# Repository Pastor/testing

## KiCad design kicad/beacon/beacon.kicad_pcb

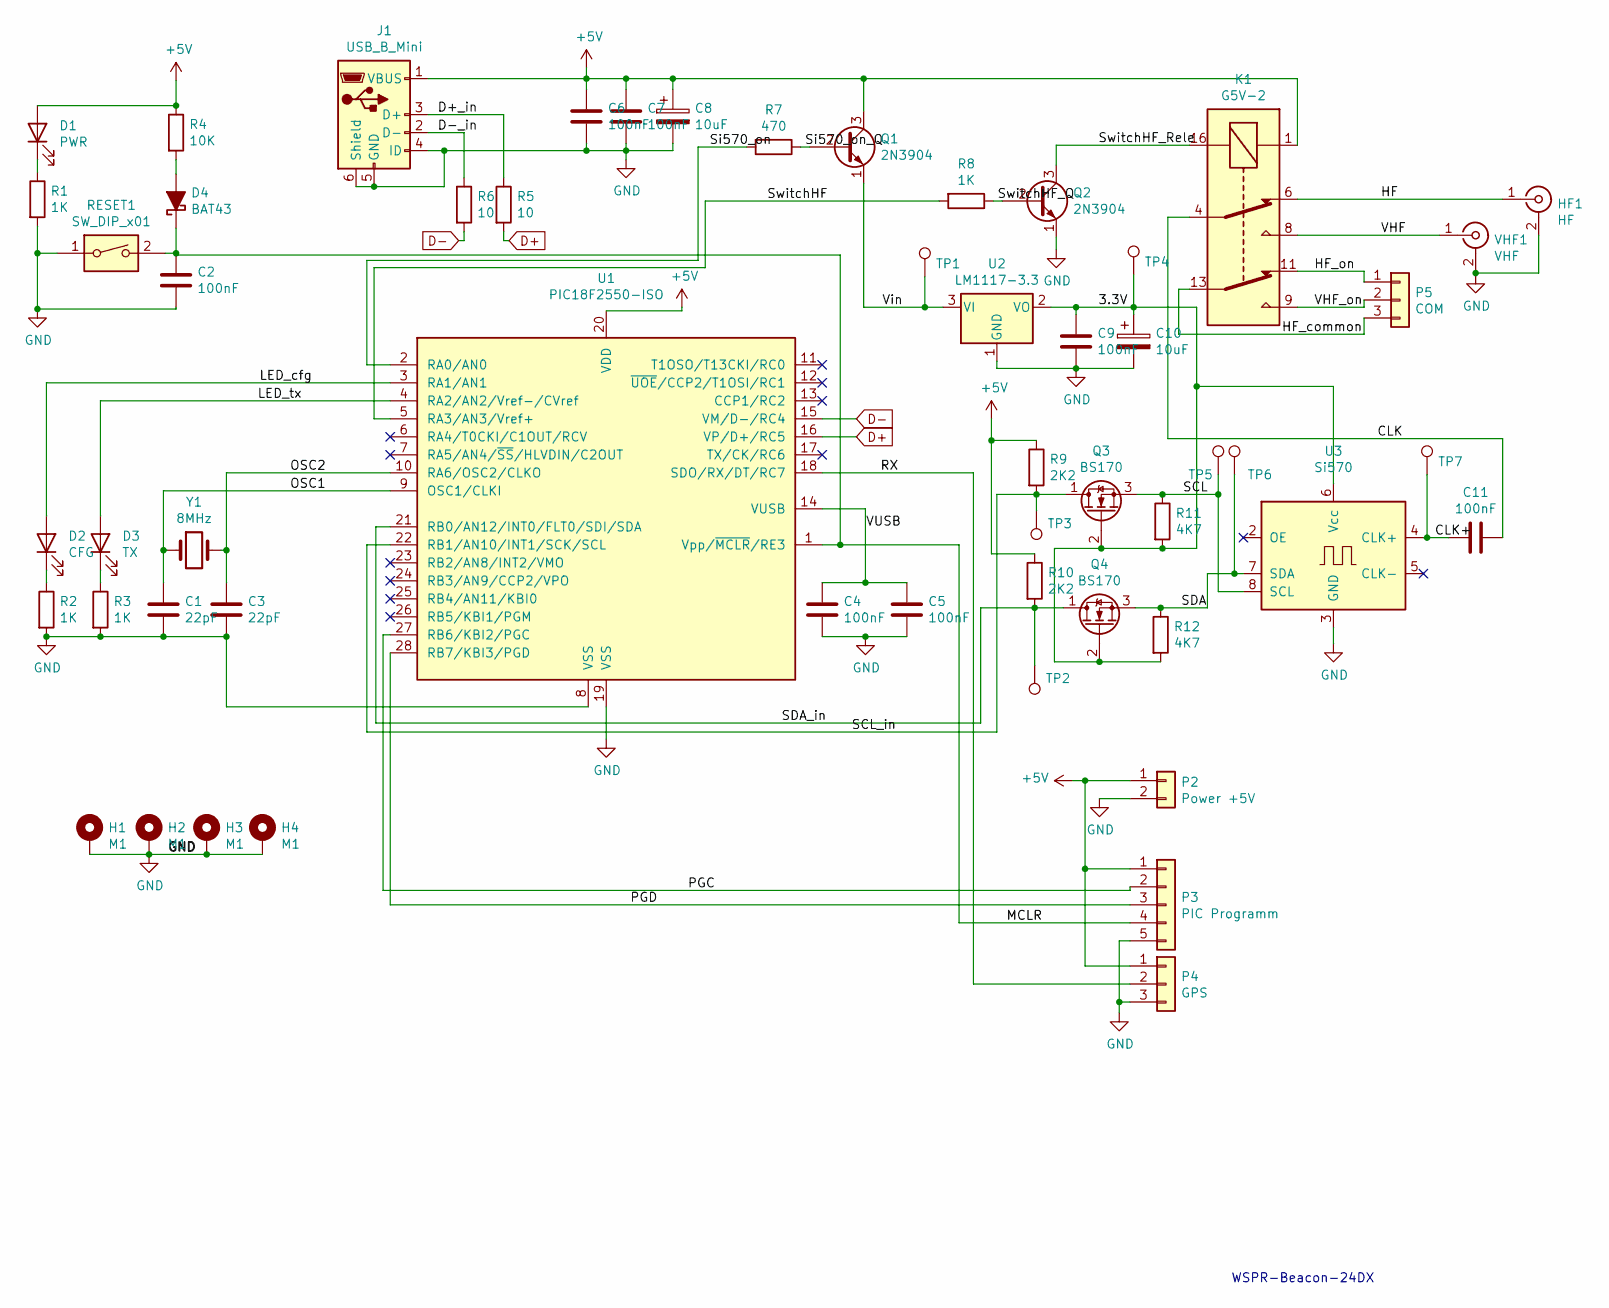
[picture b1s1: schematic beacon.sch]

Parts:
C1, C3: 22pF; C_1206_3216Metric
C2, C4, C5, C6, C7, C9, C11: 100nF; C_1206_3216Metric
C8, C10: 10uF; CP_EIA-3528-12_Kemet-T
D1: PWR; LED_Kingbright_AAA3528ESGCT
D2: CFG; LED_Kingbright_AAA3528ESGCT
D3: TX; LED_Kingbright_AAA3528ESGCT
D4: BAT43; D_DO-34_SOD68_P10.16mm_Horizontal
H1, H2, H3, H4: M1; MountingHole_3.5mm_Pad
HF1: HF; SMA_Molex_73251-1153_EdgeMount_Horizontal
J1: USB_B_Mini; USB_Mini-B_Wuerth_65100516121_Horizontal
K1: G5V-2; Relay_DPDT_Omron_G5V-2
P2: Power +5V; PinHeader_1x02_P2.54mm_Vertical
P3: PIC Programm; PinHeader_1x05_P2.54mm_Vertical
P4: GPS; PinHeader_1x03_P2.54mm_Vertical
P5: COM; PinHeader_1x03_P2.54mm_Vertical
Q1, Q2: 2N3904; TO-92_Wide
Q3, Q4: BS170; TO-92_Wide
R1, R2, R3, R8: 1K; R_1206_3216Metric
R4: 10K; R_1206_3216Metric
R5, R6: 10; R_1206_3216Metric
R7: 470; R_1206_3216Metric
R9, R10: 2K2; R_1206_3216Metric
R11, R12: 4K7; R_1206_3216Metric
RESET1: SW_DIP_x01; SW_PUSH_6mm
TP1: VI; TestPoint_Pad_D1.5mm
TP2: iSDA; TestPoint_Pad_D1.5mm
TP3: iSCL; TestPoint_Pad_D1.5mm
TP4: VO; TestPoint_Pad_D1.5mm
TP5: oSCL; TestPoint_Pad_D1.5mm
TP6: oSDA; TestPoint_Pad_D1.5mm
TP7: oCLK; TestPoint_Pad_D1.5mm
U1: PIC18F2550-ISO; SOIC-28W_7.5x17.9mm_P1.27mm
U2: LM1117-3.3; SOT-223
U3: Si570; Oscillator_SMD_SI570_SI571_Standard
VHF1: VHF; SMA_Molex_73251-1153_EdgeMount_Horizontal
Y1: 8MHz; Crystal_HC49-U_Vertical

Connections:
+5V: C6.1, C7.1, C8.1, D1.2 (A), J1.1 (VBUS), K1.1, P2.1, P3.1, P4.1, Q1.3 (C), R4.1, R9.1, R10.1, U1.20 (VDD)
/3.3V: C9.1, C10.1, Q3.2 (G), Q4.2 (G), R11.2, R12.2, TP4.1, U2.2 (VO), U3.6 (Vcc)
/CLK: C11.1, K1.4
/CLK+: C11.2, TP7.1, U3.4 (CLK+)
/D+_in: J1.3 (D+), R5.1
/D-_in: J1.2 (D-), R6.1
/HF: HF1.1 (In), K1.6
/HF_common: K1.13, P5.3
/HF_on: K1.11, P5.1
/LED_cfg: D2.2 (A), U1.3 (RA1/AN1)
/LED_tx: D3.2 (A), U1.4 (RA2/AN2/Vref-/CVref)
/MCLR: C2.1, D4.1 (K), P3.4, RESET1.2, U1.1 (Vpp/~MCLR~/RE3)
/OSC1: C1.1, U1.9 (OSC1/CLKI), Y1.1
/OSC2: C3.1, U1.10 (RA6/OSC2/CLKO), Y1.2
/PGC: P3.2, U1.27 (RB6/KBI2/PGC)
/PGD: P3.3, U1.28 (RB7/KBI3/PGD)
/RX: P4.2, U1.18 (SDO/RX/DT/RC7)
/SCL: Q3.3 (S), R11.1, TP5.1, U3.8 (SCL)
/SCL_in: Q3.1 (D), R9.2, TP3.1, U1.22 (RB1/AN10/INT1/SCK/SCL)
/SDA: Q4.3 (S), R12.1, TP6.1, U3.7 (SDA)
/SDA_in: Q4.1 (D), R10.2, TP2.1, U1.21 (RB0/AN12/INT0/FLT0/SDI/SDA)
/Si570_on: R7.2, U1.2 (RA0/AN0)
/Si570_on_Q: Q1.2 (B), R7.1
/SwitchHF: R8.2, U1.5 (RA3/AN3/Vref+)
/SwitchHF_Q: Q2.2 (B), R8.1
/SwitchHF_Rele: K1.16, Q2.3 (C)
/VHF: K1.8, VHF1.1 (In)
/VHF_on: K1.9, P5.2
/VUSB: C4.1, C5.1, U1.14 (VUSB)
/Vin: Q1.1 (E), TP1.1, U2.3 (VI)
D+: R5.2, U1.16 (VP/D+/RC5)
D-: R6.2, U1.15 (VM/D-/RC4)
GND: C1.2, C2.2, C3.2, C4.2, C5.2, C6.2, C7.2, C8.2, C9.2, C10.2, H1.1, H2.1, H3.1, H4.1, HF1.2 (Ext), J1.4 (ID), J1.5 (GND), J1.6 (Shield), P2.2, P3.5, P4.3, Q2.1 (E), R1.2, R2.2, R3.2, RESET1.1, U1.8 (VSS), U1.19 (VSS), U2.1 (GND), U3.3 (GND), VHF1.2 (Ext)
unnamed: D1.1 (K), R1.1
unnamed: D2.1 (K), R2.1
unnamed: D3.1 (K), R3.1
unnamed: D4.2 (A), R4.2

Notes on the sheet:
WSPR-Beacon-24DX

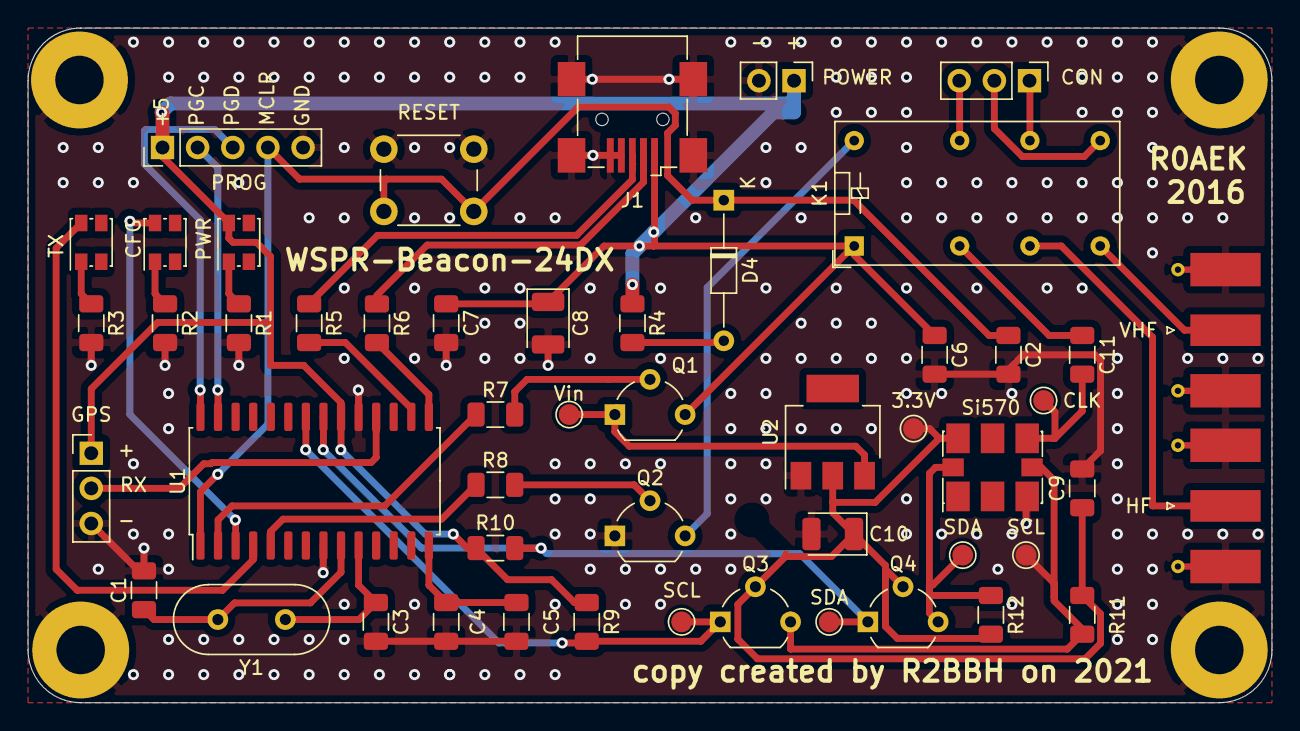
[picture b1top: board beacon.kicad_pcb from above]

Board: 2 copper layers, 89.9 x 48.8 mm, 55 parts (0 on the bottom side), 37 nets.

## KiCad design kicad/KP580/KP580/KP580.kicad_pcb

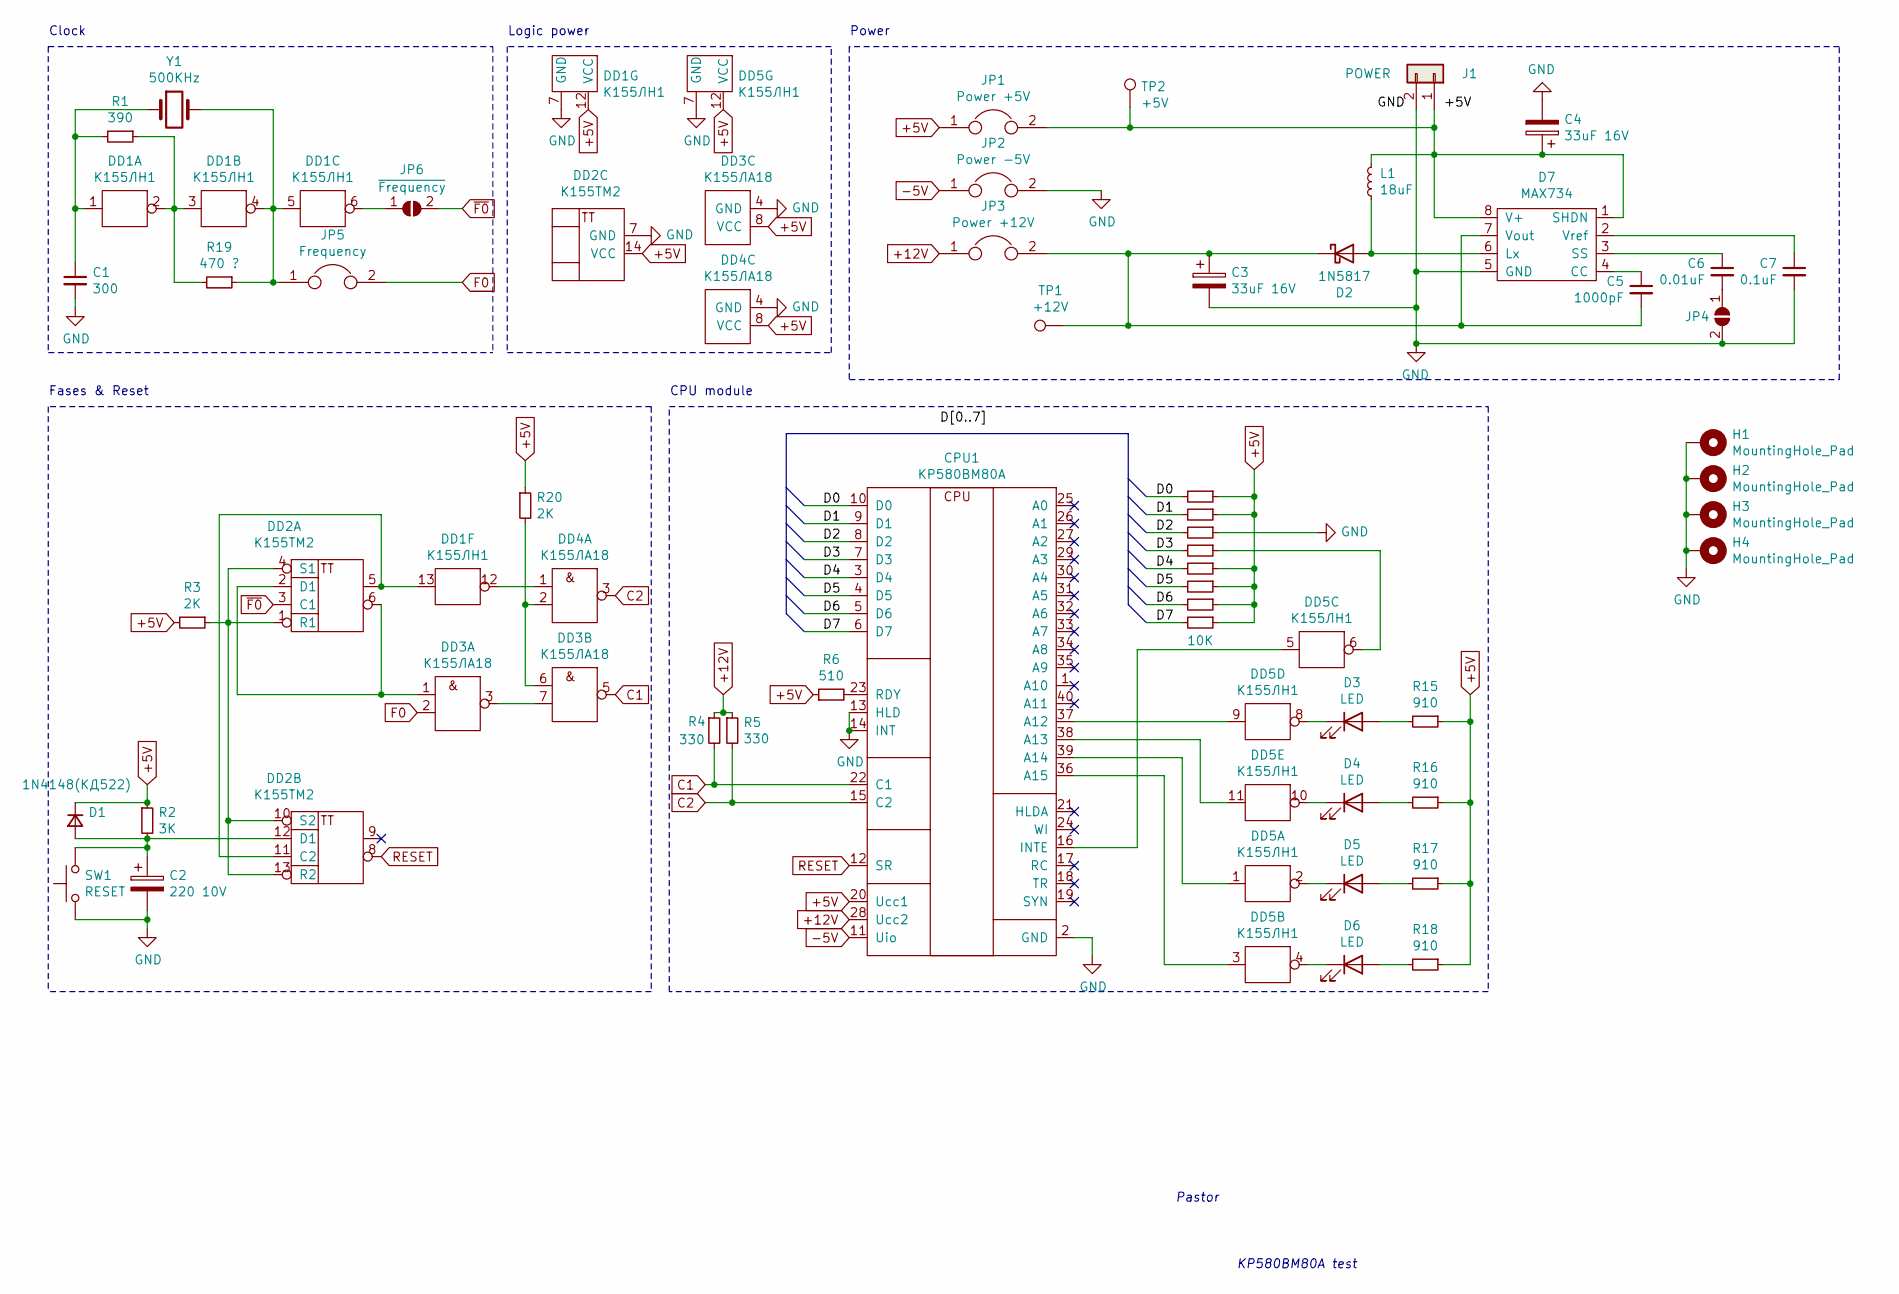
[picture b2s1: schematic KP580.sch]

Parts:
C1: 300; C_0805_2012Metric
C2: 220 10V; CP_Radial_D8.0mm_P3.50mm
C3, C4: 33uF 16V; CP_Radial_D8.0mm_P3.50mm
C5: 1000pF; C_0805_2012Metric
C6: 0.01uF; C_0805_2012Metric
C7: 0.1uF; C_0805_2012Metric
CPU1: КР580ВМ80А; DIP-40_W15.24mm
D1: 1N4148(КД522); D_DO-35_SOD27_P7.62mm_Horizontal
D2: 1N5817; D_DO-35_SOD27_P7.62mm_Horizontal
D3, D4, D5, D6: LED; LED_D5.0mm_Clear
D7: MAX734; DIP-8_W7.62mm
DD1, DD5: К155ЛН1; DIP-14_W7.62mm
DD2: K155TM2; DIP-14_W7.62mm
DD3, DD4: К155ЛА18; DIP-8_W7.62mm
H1, H2, H3, H4: MountingHole_Pad; MountingHole_2.7mm_Pad_Via
J1: POWER; PinHeader_2x01_P2.54mm_Vertical
JP1: Power +5V; PinHeader_2x01_P2.54mm_Vertical
JP2: Power -5V; PinHeader_2x01_P2.54mm_Vertical
JP3: Power +12V; PinHeader_2x01_P2.54mm_Vertical
JP4: SolderJumper-2_P1.3mm_Open_RoundedPad1.0x1.5mm
JP5: Frequency; PinHeader_2x01_P2.54mm_Vertical
JP6: ~Frequency; SolderJumper-2_P1.3mm_Open_RoundedPad1.0x1.5mm
L1: 18uF; L_Axial_L7.0mm_D3.3mm_P10.16mm_Horizontal_Fastron_MICC
R1: 390; R_0805_2012Metric
R2: 3K; R_0805_2012Metric
R3, R20: 2K; R_0805_2012Metric
R4, R5: 330; R_0805_2012Metric
R6: 510; R_0805_2012Metric
R7, R8, R9, R10, R11, R12, R13, R14: 10K; R_0805_2012Metric
R15, R16, R17, R18: 910; R_0805_2012Metric
R19: 470 ?; R_0805_2012Metric
SW1: RESET; SW_SPST_TL3305A
TP1: +12V; TestPoint_Pad_D1.5mm
TP2: +5V; TestPoint_Pad_D1.5mm
Y1: 500KHz; Crystal_HC18-U_Vertical

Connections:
+12V: CPU1.28 (Ucc2), JP3.1, R4.1, R5.1
-5V: CPU1.11 (Uio), JP2.1
/D0: CPU1.10 (D0), R7.2
/D1: CPU1.9 (D1), R8.2
/D2: CPU1.8 (D2), R9.2
/D3: CPU1.7 (D3), R10.2
/D4: CPU1.3 (D4), R11.2
/D5: CPU1.4 (D5), R12.2
/D6: CPU1.5 (D6), R13.2
/D7: CPU1.6 (D7), R14.2
C1: CPU1.22 (C1), DD3.5, R4.2
C2: CPU1.15 (C2), DD4.3, R5.2
F0: DD3.2, JP5.2
GND: C1.2, C2.2, C3.2, C4.2, C7.2, CPU1.2 (GND), CPU1.13 (HLD), CPU1.14 (INT), D7.5 (GND), DD1.7 (GND), DD2.7 (GND), DD3.4 (GND), DD4.4 (GND), DD5.7 (GND), H1.1, H2.1, H3.1, H4.1, J1.2, JP2.2, JP4.2 (B), R9.1, SW1.1
unnamed: C1.1, DD1.1, R1.2, Y1.1
unnamed: C2.1, D1.2 (A), DD2.12 (D1), R2.2, SW1.2
unnamed: C3.1, C5.2, D2.1 (K), D7.7 (Vout), JP3.2, TP1.1
unnamed: C4.1, D7.1 (SHDN), D7.8 (V+), J1.1, JP1.2, L1.2, TP2.1
unnamed: C5.1, D7.4 (CC)
unnamed: C6.1, D7.3 (SS)
unnamed: C6.2, JP4.1 (A)
unnamed: C7.1, D7.2 (Vref)
unnamed: CPU1.16 (INTE), DD5.5
unnamed: CPU1.23 (RDY), R6.2
unnamed: CPU1.36 (A15), DD5.3
unnamed: CPU1.37 (A12), DD5.9
unnamed: CPU1.38 (A13), DD5.11
unnamed: CPU1.39 (A14), DD5.1
unnamed: D2.2 (A), D7.6 (Lx), L1.1
unnamed: D3.1 (K), DD5.8
unnamed: D3.2 (A), R15.2
unnamed: D4.1 (K), DD5.10
unnamed: D4.2 (A), R16.2
unnamed: D5.1 (K), DD5.2
unnamed: D5.2 (A), R17.2
unnamed: D6.1 (K), DD5.4
unnamed: D6.2 (A), R18.2
unnamed: DD1.2, DD1.3, R1.1, R19.2
unnamed: DD1.4, DD1.5, JP5.1, R19.1, Y1.2
unnamed: DD1.6, JP6.1 (A)
unnamed: DD1.13, DD2.5, DD2.11 (C2)
unnamed: DD2.1 (R1), DD2.4 (S1), DD2.10 (S2), DD2.13 (R2), R3.1
unnamed: DD2.2 (D1), DD2.6, DD3.1
unnamed: DD3.3, DD3.7
unnamed: DD3.6, DD4.2, R20.2
unnamed: DD5.6, R10.1
RESET: CPU1.12 (SR), DD2.8
~F0: DD2.3 (C1), JP6.2 (B)

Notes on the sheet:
Clock
Fases & Reset
CPU module
Power
KP580BM80A test
Pastor
Logic power

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
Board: 2 copper layers, 54 parts (0 on the bottom side), 49 nets, no tracks yet.

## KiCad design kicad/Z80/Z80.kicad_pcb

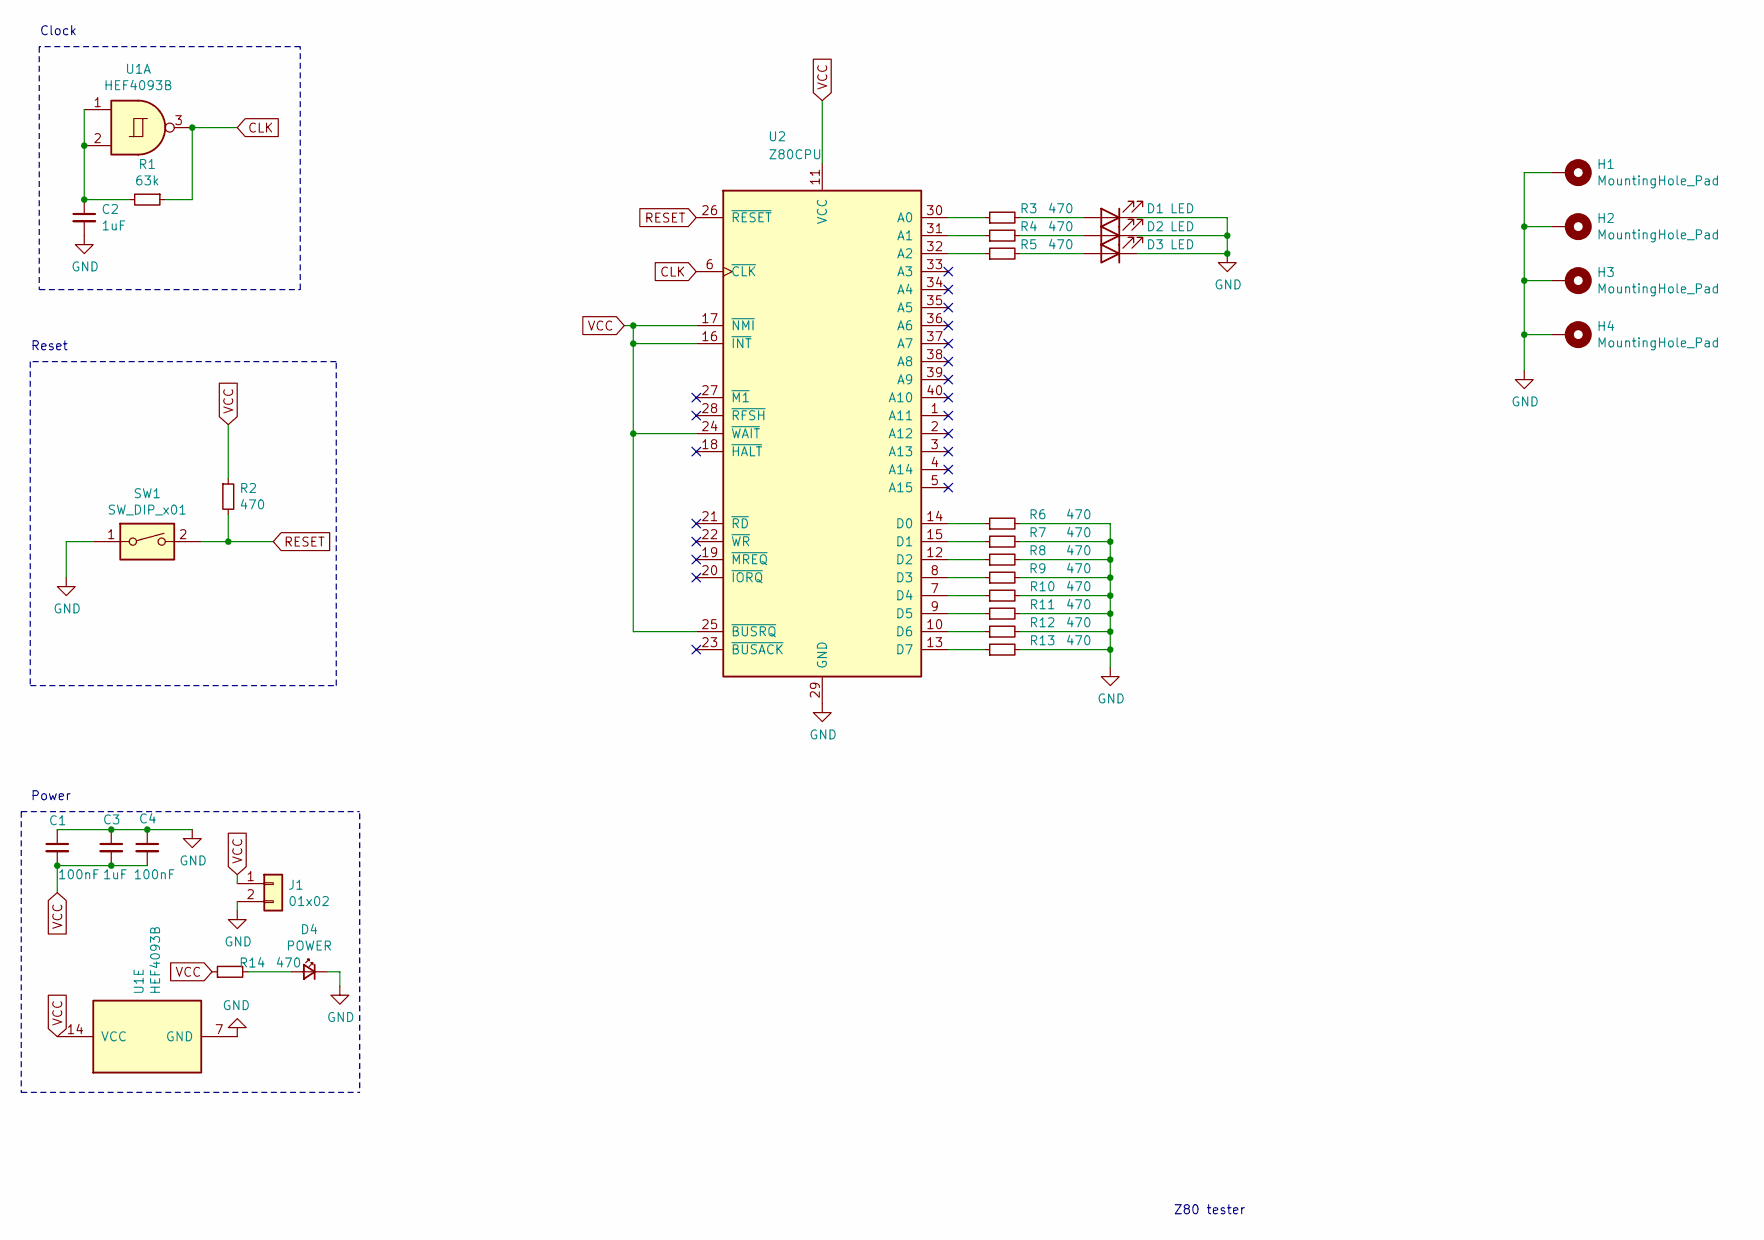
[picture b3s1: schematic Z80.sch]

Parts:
C1, C4: 100nF; C_0805_2012Metric
C2, C3: 1uF; C_0805_2012Metric
D1, D2, D3: LED; LED_D5.0mm_Clear
D4: POWER; LED_1206_3216Metric
H1, H2, H3, H4: MountingHole_Pad; MountingHole_4.3mm_M4_Pad_Via
J1: 01x02; PinHeader_1x02_P2.54mm_Vertical
R1: 63k; R_0805_2012Metric
R2, R3, R4, R5, R6, R7, R8, R9, R10, R11, R12, R13, R14: 470; R_0805_2012Metric
SW1: SW_DIP_x01; SW_SPST_EVPBF
U1: HEF4093B; DIP-14_W7.62mm_Socket
U2: Z80CPU; DIP-40_W15.24mm_Socket

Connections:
CLK: R1.1, U1.3, U2.6 (~CLK~)
GND: C1.1, C2.2, C3.1, C4.1, D1.1 (K), D2.1 (K), D3.1 (K), D4.1 (K), H1.1, H2.1, H3.1, H4.1, J1.2, R6.2, R7.2, R8.2, R9.2, R10.2, R11.2, R12.2, R13.2, SW1.1, U1.7 (GND), U2.29 (GND)
unnamed: C2.1, R1.2, U1.1, U1.2
unnamed: D1.2 (A), R3.2
unnamed: D2.2 (A), R4.2
unnamed: D3.2 (A), R5.2
unnamed: D4.2 (A), R14.2
unnamed: R3.1, U2.30 (A0)
unnamed: R4.1, U2.31 (A1)
unnamed: R5.1, U2.32 (A2)
unnamed: R6.1, U2.14 (D0)
unnamed: R7.1, U2.15 (D1)
unnamed: R8.1, U2.12 (D2)
unnamed: R9.1, U2.8 (D3)
unnamed: R10.1, U2.7 (D4)
unnamed: R11.1, U2.9 (D5)
unnamed: R12.1, U2.10 (D6)
unnamed: R13.1, U2.13 (D7)
RESET: R2.2, SW1.2, U2.26 (~RESET~)
VCC: C1.2, C3.2, C4.2, J1.1, R2.1, R14.1, U1.14 (VCC), U2.11 (VCC), U2.16 (~INT~), U2.17 (~NMI~), U2.24 (~WAIT~), U2.25 (~BUSRQ~)

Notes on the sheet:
Z80 tester
Clock
Reset
Power

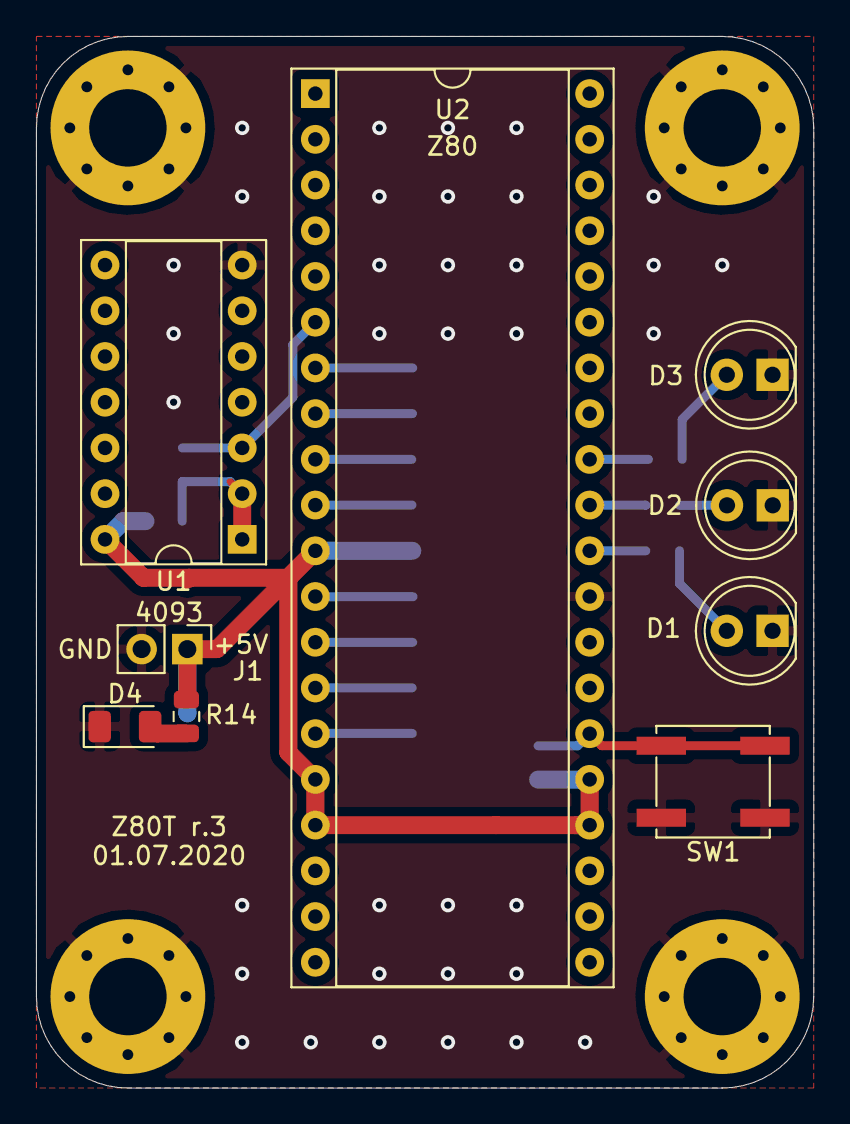
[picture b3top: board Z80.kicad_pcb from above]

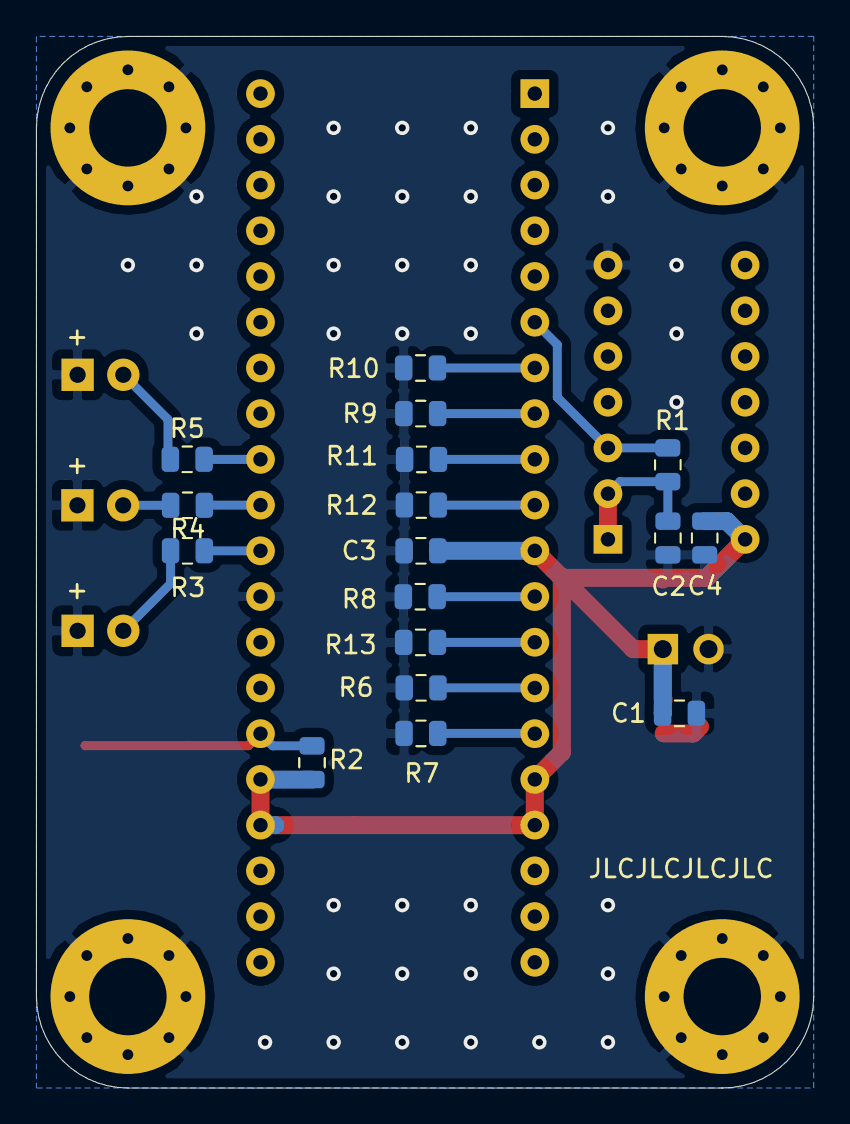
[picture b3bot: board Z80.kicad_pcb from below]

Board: 2 copper layers, 43.2 x 58.4 mm, 30 parts (17 on the bottom side), 20 nets.

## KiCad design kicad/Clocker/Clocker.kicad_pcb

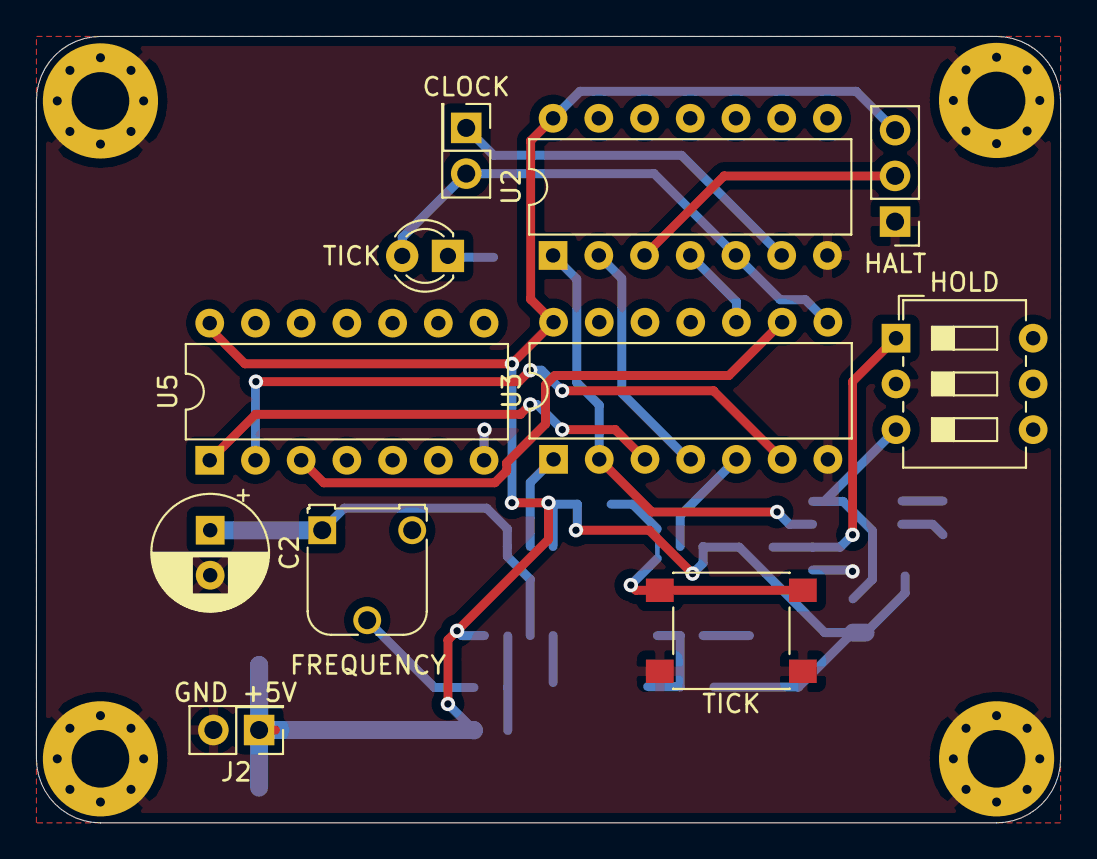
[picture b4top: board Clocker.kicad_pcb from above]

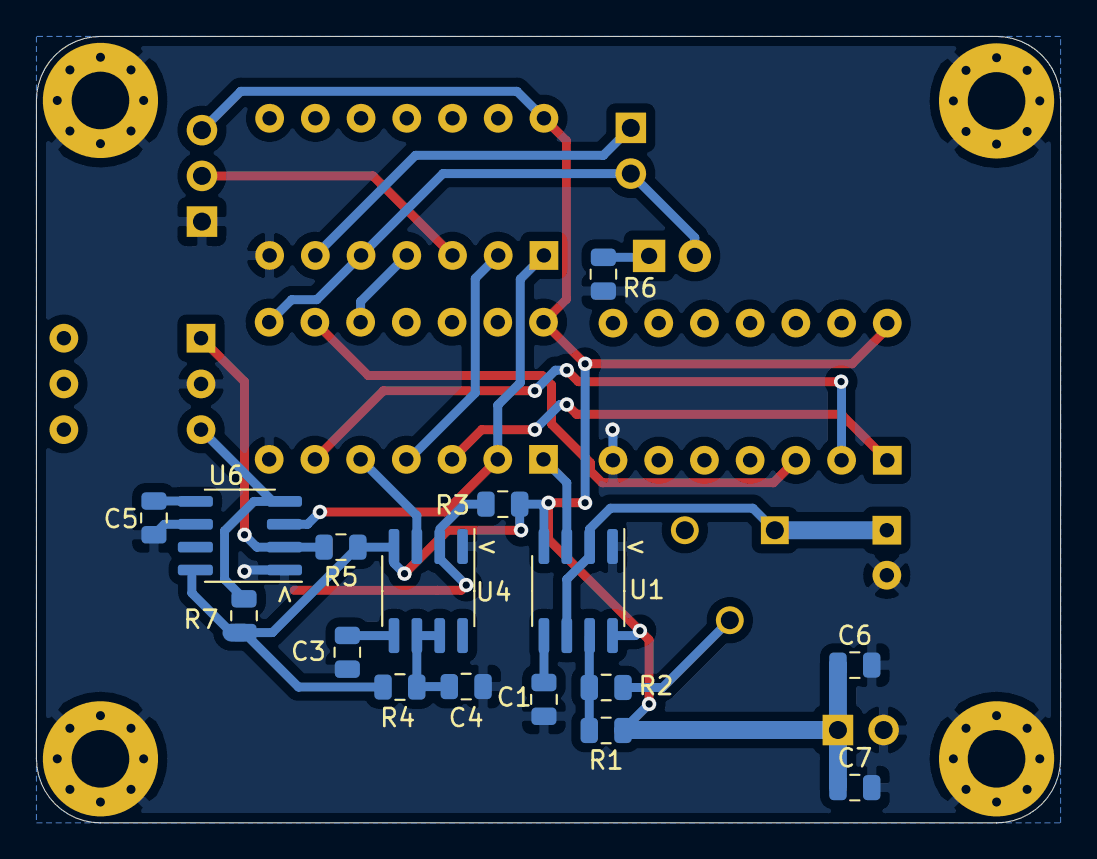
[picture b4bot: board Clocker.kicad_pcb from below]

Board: 2 copper layers, 56.9 x 43.7 mm, 31 parts (16 on the bottom side), 24 nets.

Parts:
C1, C3, C5: 0.01uF; C_0805_2012Metric
C2: 1uF 10V; CP_Radial_D6.3mm_P2.50mm
C4, C6, C7: 0.1uF; C_0805_2012Metric
CLOCK: Clock; PinHeader_2x01_P2.54mm_Vertical
FREQUENCY: 1M; Potentiometer_Runtron_RM-065_Vertical
H1, H2, H3, H4: MountingHole_Pad; MountingHole_3.2mm_M3_Pad_Via
HALT: Halt; PinHeader_1x03_P2.54mm_Vertical
HOLD: Lock; SW_DIP_SPSTx03_Slide_6.7x9.18mm_W7.62mm_P2.54mm_LowProfile
J2: Power; PinHeader_2x01_P2.54mm_Vertical
R1, R2, R3, R5, R7: 1K; R_0805_2012Metric
R4: 1M; R_0805_2012Metric
R6: 220; R_0805_2012Metric
TICK: BLUE; LED_D3.0mm_Clear
TICK#2: SW_Push; SW_Push_1P1T_NO_6x6mm_H9.5mm
U1, U4, U6: LM555xM; SOIC-8_3.9x4.9mm_P1.27mm
U2: 74LS04; DIP-14_W7.62mm
U3: 74LS08; DIP-14_W7.62mm
U5: 74LS32; DIP-14_W7.62mm

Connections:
+5V: C6.1, C7.1, HALT.3, J2.1, R1.1, R3.1, R4.1, R5.1, R7.1, U1.4, U1.8, U2.14, U3.14, U4.4, U5.14, U6.8
CLK: CLOCK.2, TICK.2, U2.5, U3.8
GND: C1.2, C2.2, C3.2, C4.2, C5.2, C6.2, C7.2, H1.1, H2.1, H3.1, H4.1, HALT.1, HOLD.2, J2.2, R6.2, TICK#2.1, U1.1, U2.7, U3.7, U4.1, U5.7, U6.1, U6.6
HLT: HALT.2, U2.3
unnamed: C1.1, U1.5
unnamed: C2.1, FREQUENCY.1, U1.2, U1.6
unnamed: C3.1, U4.5
unnamed: C4.1, R4.2, U4.6, U4.7
unnamed: C5.1, U6.5
unnamed: R6.1, TICK.1
unnamed: R1.2, R2.2, U1.7
unnamed: FREQUENCY.2, R2.1
unnamed: R3.2, TICK#2.2, U4.2
unnamed: HOLD.1, R5.2, U6.2
unnamed: HOLD.3, R7.2, U6.4
unnamed: U1.3, U3.1
unnamed: U2.1, U3.2, U6.3
unnamed: U2.2, U3.4
unnamed: U2.4, U3.10
unnamed: U3.3, U5.1
unnamed: U3.5, U4.3
unnamed: U3.6, U5.2
unnamed: U3.9, U5.3
~CLK: CLOCK.1, U2.6

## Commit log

2017-07-02 GoLang: restful api and sqlite3 tests
2017-07-02 Rustlang mini_resful_db sample
2017-07-02 Тестирование
2017-07-03 Reformat
2017-07-03 Добавлен шаблон для cplusplus
2017-11-21 Немного тестов
2017-11-21 Немного исправлений
2017-11-21 error_code, error_message
2017-11-21 Добавлен кэш
2017-11-21 Подключена проверка etcd
2017-11-22 Изменения
2017-12-07 Telegram bot
2017-12-07 vm8080
2018-12-26 renaming
2018-12-29 Rust http server testing
2019-01-05 stm8
2019-01-07 ATCA
2019-02-15 Add stm8s
2019-02-17 STM32. LED standard library
2019-03-06 пример с libmicrohttpd
2019-03-23 TinyCC
2019-03-25 Received http chunk
2019-03-26 for macosx
2019-03-27 Unix compile JM TCC server
2019-03-27 Append libraries to Unix
2019-04-06 STM8: Mein flow
2019-04-07 STM8: linux try
2019-04-12 STM8: I2C
2019-04-12 Bananapi: init
2019-04-13 Bananapi: dependencies
2019-05-16 compile sqlite3
2019-05-27 Файл конфигурации
2019-09-15 Example static resources
2019-10-05 Тестовое API для проверки KrakenD API Gateway
2019-10-05 Добавление CORS
2019-10-06 Плагин для KrakenD
2019-10-06 Настройки KrakenD и модули проверки CEL
2019-10-07 Token requester
2019-10-07 Colorized log
2019-10-08 Authorized client
2019-10-09 Добавлен метод developers
2019-10-11 Конфигурация для Krakend - раздельная
2019-10-11 KrakenD configuration template
2019-10-23 Тест для проверки GatewayAPI
2019-10-24 Корректировка тестов для проверки GatewayAPI
2019-11-01 Botan CA, CRL example
2019-11-03 Botan для MinGW
2019-11-06 Secure C samples
2019-12-19 Загрузка файлов в minio
2019-12-25 Формирование задания для студентов
2019-12-26 Расчет задания на курсовую
2019-12-28 FORTH
2019-12-30 F18Y
2019-12-30 F18Y.LOG
2020-01-01 Добавление примеров
2020-01-01 CMakeLists.txt for STM8 projects
2020-01-02 Сохранение состояния
2020-01-08 F32A
2020-01-08 Search I2C device
2020-01-08 memory trap
2020-01-09 Complete I2C working
2020-01-09 Try search I2C working algorithm
2020-01-10 Change to 24C02
2020-01-14 Chnage emulator place and
2020-01-14 Windows fix
2020-01-14 Изменение типов входных параметров функций разбора входной последовательности на char
2020-01-17 Empty stream server
2020-01-17 Включение подстановки URL для debug режима
2020-01-18 find BUG
2020-01-19 Поиск в архиве
2020-01-19 Небольшие изаменения
2020-01-28 Исправление ошибки
2020-02-27 Сортировка разная всякая
2020-02-27 Вывести на экран только числа из созданного Вами на диске текстового файла, содержащего буквы и числа
2020-02-27 Решето Эратосфена
2020-02-28 Удивительные номера
2020-03-05 Замена символов
2020-03-07 notification init
2020-03-09 notification continue. Part 2
2020-03-09 notification continue. Part 3
2020-03-14 Intel HEX format
2020-03-14 Intel HEX format complete
2020-03-16 Правильная обработка окончания файла или строки
2020-04-25 stm8s change and more other
2020-04-28 Embedded Rust STM32
2020-05-02 Отправка почты GoLang
2020-05-05 android sms poll
2020-05-07 Полный sms poll
2020-05-07 Отображение ошибки
2020-05-08 Изменение таймаутов
2020-05-08 Изменен текст оповещения
2020-05-11 ZTE firmware
2020-05-13 Добавлен отлов исключения при ошибках сети
2020-05-13 Altium + FPGA
2020-06-06 KiCAD Z80 testing
2020-06-07 Z80 tester complete
2020-06-21 add FPGA
2020-08-23 notification continue. Part 4
2020-11-05 Генератор курсовых работ
2020-11-25 APRS tests
2021-03-25 Beacon
2021-03-30 Simple FPGA project
2021-03-31 Bump guava from 28.1-jre to 29.0-jre in /java/lightweight-http
    Bumps [guava](https://github.com/google/guava) from 28.1-jre to 29.0-jre.
    - [Release notes](https://github.com/google/guava/releases)
    - [Commits](https://github.com/google/guava/commits)
2021-04-09 Abb robo
2021-04-10 Append abb api template
2021-04-16 Добавлен сторонний интерфейс ABB, добавлено сохранение информации о чатах
2021-04-16 Добавлено сохранение сообщений
2021-04-18 Компановка функций
2021-04-20 Release в случае падения
2021-04-21 ABB логирование JSON
2021-04-23 Выделение из проекта библиотеку и исполняемый модуль + переименование проекта
2021-04-23 Dll SimInTech на Rust
2021-04-27 Mastership requests
2021-06-07 APRS simple
2021-06-10 APRS logging
2021-06-29 Kotlin: ktor oauth2
